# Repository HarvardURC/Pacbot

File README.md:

# PacBot
Repository for the Harvard Undergraduate Robotics Club's PacBot team

> NOTE: Because this repository includes submodules, it should be cloned using `git clone --recursive`.

The rules for PacBot and helpful images can be found at our website: https://harvardrobotics.com/pacbots

Codebase for 2021-2022 can be found in the ***master*** branch. Codebases for past years can be found in their respective branches.

The current Pacman game code can be found in 'src/gameEngine'. The README there describes how to run the game.

The code for the Harvard robotics team's bot can be found in the 'src/botCode' folder (if you're looking for inspiration).

Documentation for participating teams regarding the game board/arena, bot designs from past years, and how to communicate with the game can be found in the 'docs' directory. Baseline code is provided here that teams can use to code their bots.

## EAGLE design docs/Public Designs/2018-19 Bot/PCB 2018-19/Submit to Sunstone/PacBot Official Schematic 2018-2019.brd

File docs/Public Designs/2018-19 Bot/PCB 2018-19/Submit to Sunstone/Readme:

LAYER DESCRIPTIONS

tplace (21), tnames (25): Top silk layer

bplace (22), bnames (26): Bottom silk layer

holes (45): Reference for where holes should be placed so that PCB can be fastened by nut and bolt

reference (49): For personal reference (not to be printed)

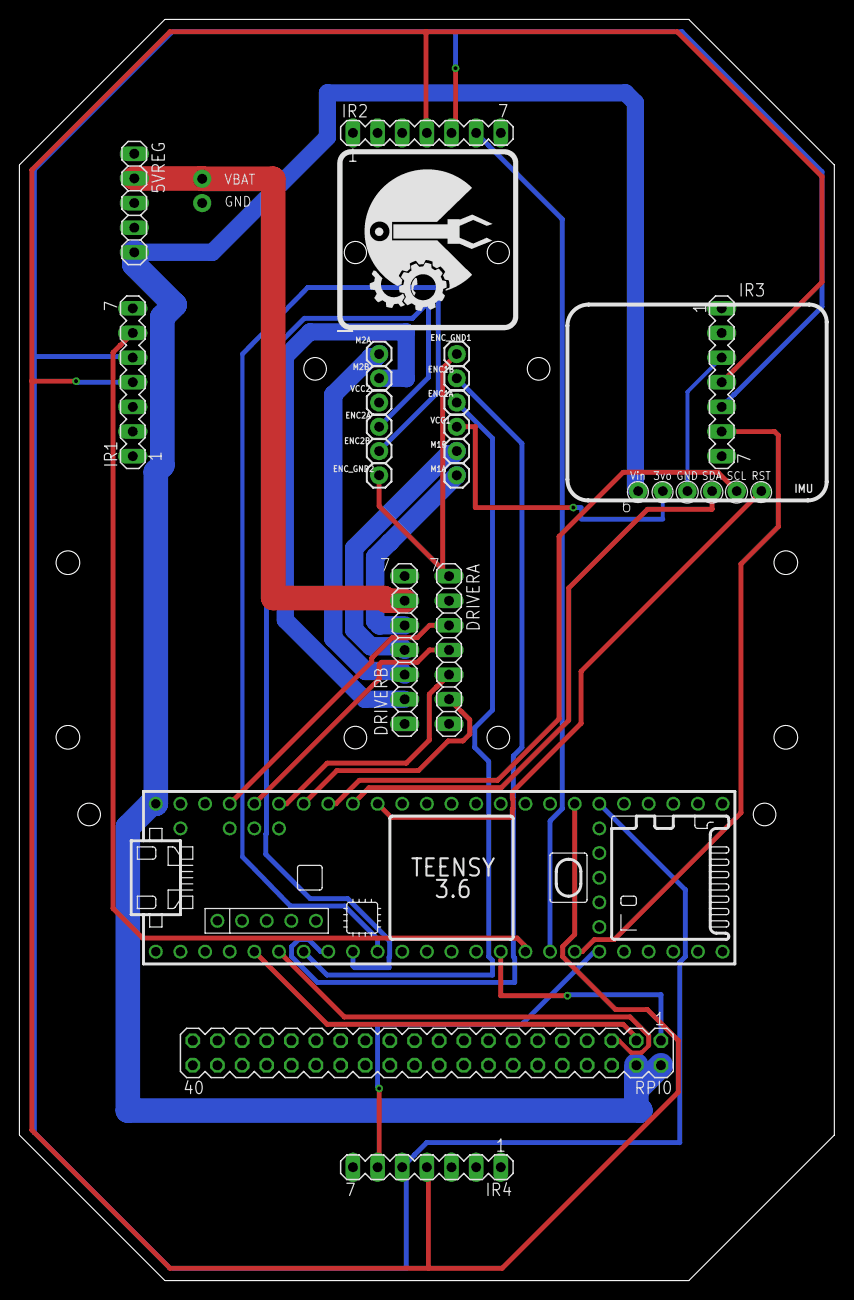
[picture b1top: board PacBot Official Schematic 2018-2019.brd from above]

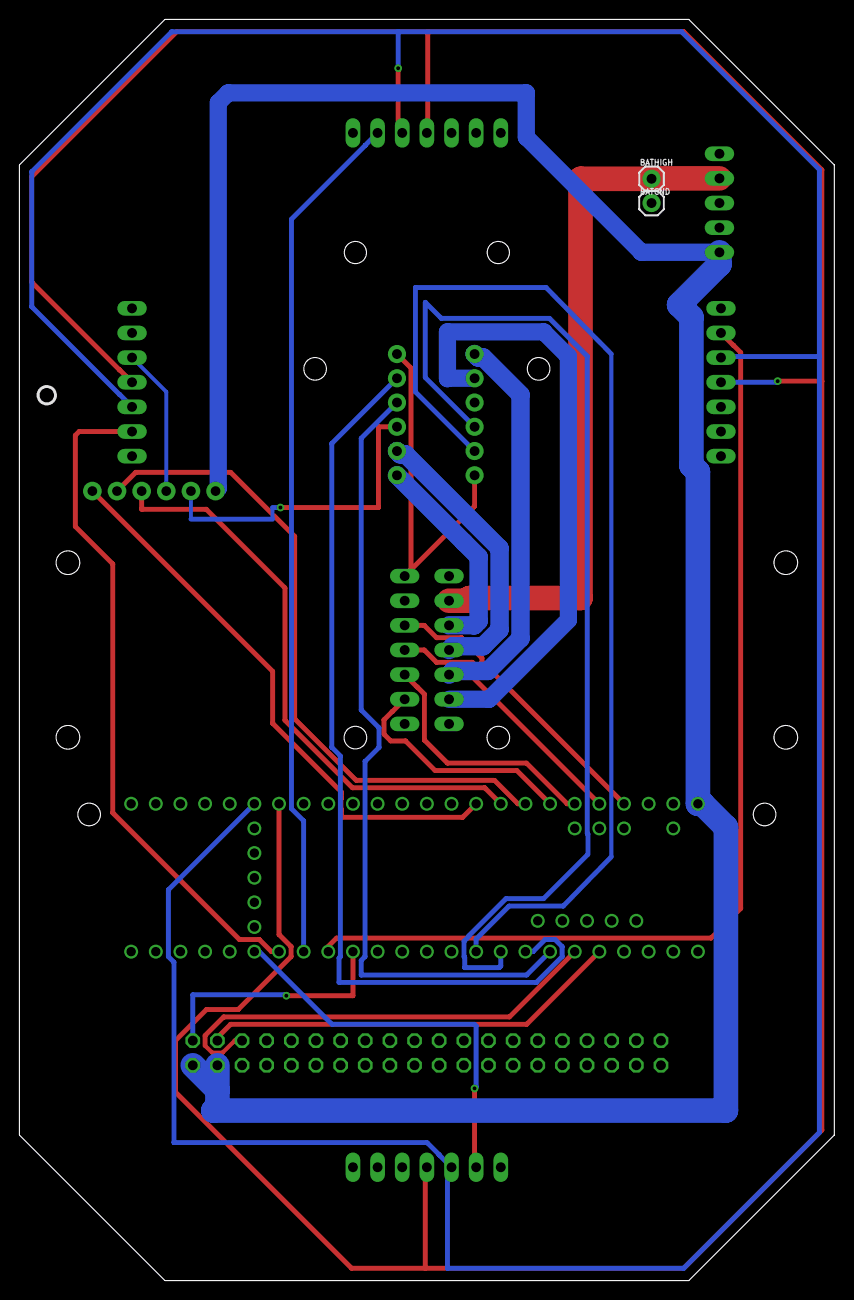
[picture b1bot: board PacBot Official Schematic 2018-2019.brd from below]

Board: 2 copper layers, 84.0 x 130.0 mm, 25 parts (3 on the bottom side), 27 nets.

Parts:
5VREG: 1X05
BATGND: 1X01
BATHIGH: 1X01
DRIVERA: 1X07
DRIVERB: 1X07
ENC1A, ENC1B, ENC2A, ENC2B: 1X01
ENC_GND1, ENC_GND2: 1X01
IMU: 1X06_ROUND_76
IR1, IR2, IR3, IR4: MA07-1
M1A, M1B, M2A, M2B: 1X01
RPI0: MA20-2
U$1: TEENSY_3.5/3.6
U$65: PCBFEAT-REV-040
VCC1, VCC2: 1X01

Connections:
3.3V: DRIVERA.2, DRIVERA.7, IMU.2, IR1.2, IR2.2, IR3.2, IR4.2, RPI0.1, U$1.3V3, U$1.3V3_LO, VCC1.1, VCC2.1
5.0V: 5VREG.5, IMU.1, RPI0.2, RPI0.4, U$1.VIN
AENBL: DRIVERA.5, U$1.21/A7
APHASE: DRIVERA.6, U$1.20/A6
BENBL: DRIVERA.3, U$1.23/A9
BPHASE: DRIVERA.4, U$1.22/A8
GND: 5VREG.3, 5VREG.4, BATGND.1, DRIVERA.1, DRIVERB.7, ENC_GND1.1, ENC_GND2.1, IMU.3, IR1.3, IR2.3, IR3.3, IR4.3, RPI0.6, RPI0.9, RPI0.14, RPI0.20, RPI0.25, RPI0.30, RPI0.34, RPI0.39, U$1.AGND, U$1.GND, U$1.GND2
unnamed: ENC1A.1, U$1.5
unnamed: IR2.6, U$1.25
unnamed: RPI0.3, U$1.3/CANTX
unnamed: IR3.6, U$1.26
unnamed: ENC1B.1, U$1.6
unnamed: RPI0.5, U$1.4/CANRX
unnamed: IR4.6, U$1.27
unnamed: DRIVERB.5, M1A.1
unnamed: DRIVERB.4, M1B.1
unnamed: DRIVERB.3, M2A.1
unnamed: DRIVERB.2, M2B.1
unnamed: ENC2A.1, U$1.7
unnamed: ENC2B.1, U$1.8
unnamed: IR1.6, U$1.24
RST_5V: IMU.6, U$1.17/A3
SCL1: IR1.5, IR2.5, IR3.5, IR4.5, U$1.38/A19
SCL_5V: IMU.5, U$1.19/A5/SCL
SDA1: IR1.4, IR2.4, IR3.4, IR4.4, U$1.39/A20
SDA_5V: IMU.4, U$1.18/A4/SDA
VBAT: 5VREG.2, BATHIGH.1, DRIVERB.6

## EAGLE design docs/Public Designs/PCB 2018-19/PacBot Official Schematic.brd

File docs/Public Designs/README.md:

# Harvard PacBot Design Overview 2018-19
(PCB design files and schematic can be found in public PacBot Design Folder)

## Electrical Components
-1 Raspberry Pi Zero W

-1 Teensy 3.5

-1 PCB

-1 IMU

-Assorted capacitors, resistors, wires

-4 IR Sensors

-2 Magnetic encoder pairs

-2 Motors

-1 Motor Driver

-Li-Po Battery

(specific links to components can be found at https://docs.google.com/spreadsheets/d/1ZO9OBoGcNkOdx6GaBkAFo6AWodeVCOaCXKic-0er2z0/edit?usp=sharing)

## Mechanical Components
-Wheels/Ball Casters

-3D Printed Battery Clip

## Code
All code can be found in the accompanying folders in this repo. We recommend looking at code from 2018-2019 because this year's code will be undergoing maintenance between now and the competition.

## Broad Overview
As the core processors for the bot, a Raspberry Pi Zero W and Teensy 3.5 were used. Nearly all of our high level and low level code ran off of our Raspberry Pi Zero W; the teensy was mainly used to interface with the encoders and other sensors. The entire bot was centered around the PCB. The motors directly attached to the PCB using small brackets, and all of the electrical components were soldered on in some manner. Although the schematic of the electrical components and the PCB design (which are in this folder) give an idea of the set up of our bot, we unfortunately do not have a SolidWorks design of our 2018-19 bot. A few photos of the 2018-19 bot in this folder help give a picture of the overall design. Further information (including a SolidWorks cad file) regarding our 2020-21 bot will be provided soon to supplement this overview.

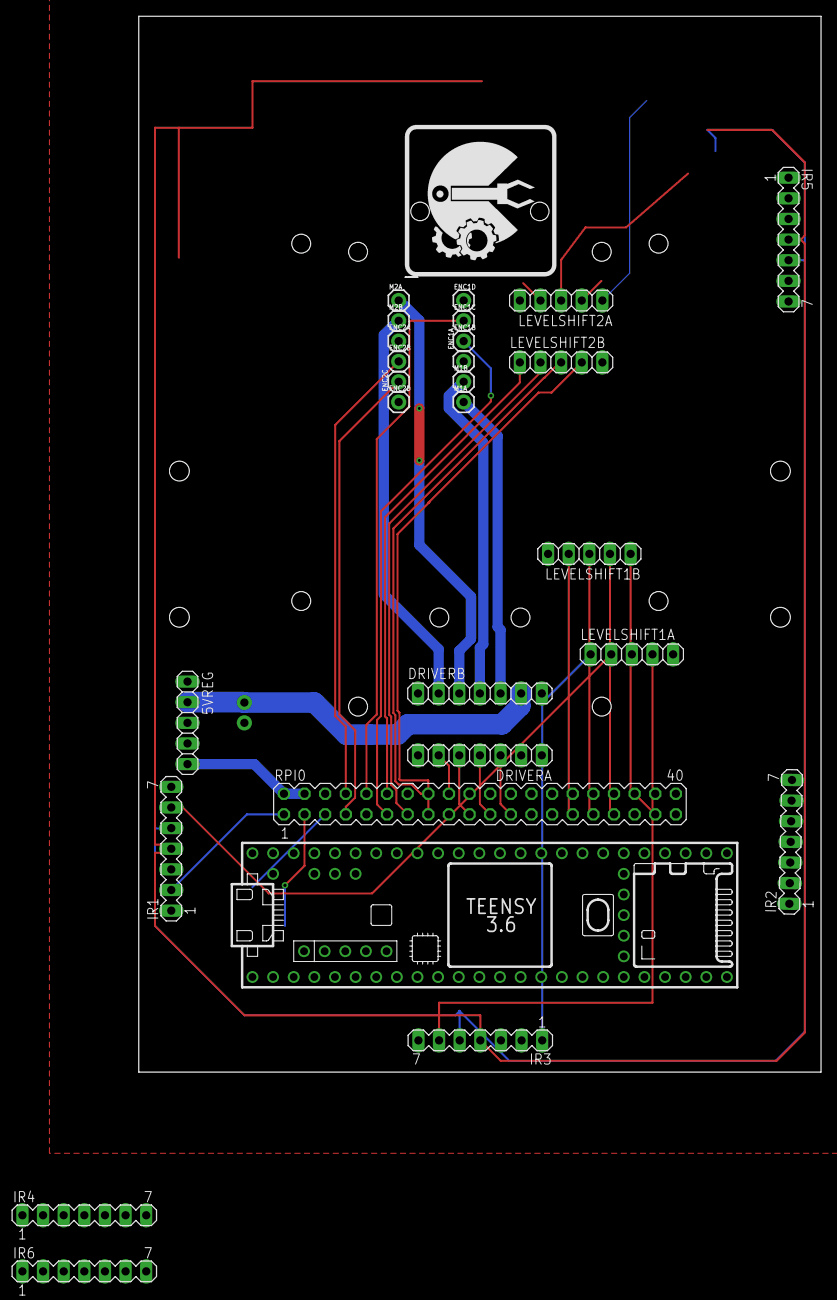
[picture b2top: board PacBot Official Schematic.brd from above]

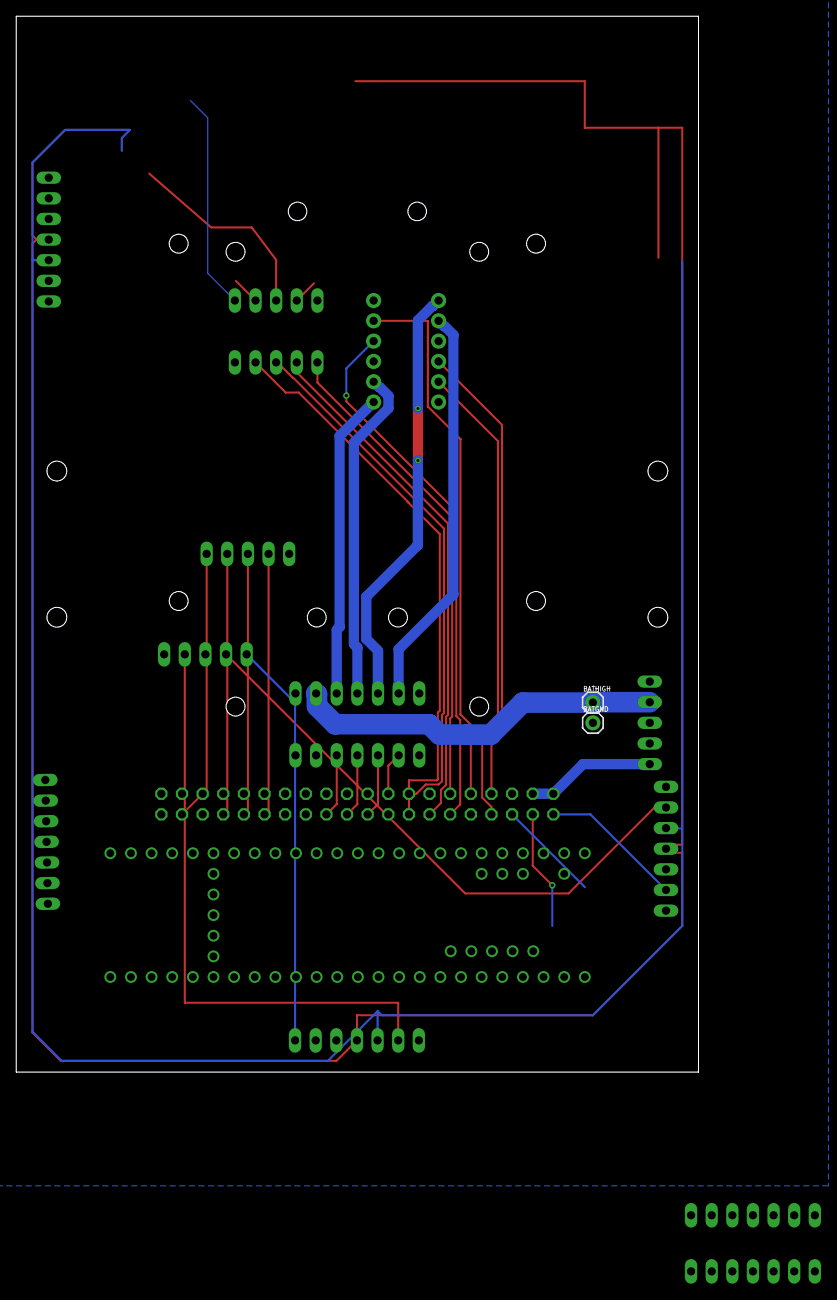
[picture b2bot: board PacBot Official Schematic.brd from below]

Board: 2 copper layers, 84.0 x 130.0 mm, 29 parts (2 on the bottom side), 32 nets.

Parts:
5VREG: 1X05
BATGND: 1X01
BATHIGH: 1X01
DRIVERA: 1X07
DRIVERB: 1X07
ENC1A, ENC1B, ENC1C, ENC1D, ENC2A, ENC2B, ENC2C, ENC2D: 1X01
IR1, IR2, IR3, IR4, IR5, IR6: MA07-1
LEVELSHIFT1A, LEVELSHIFT1B, LEVELSHIFT2A, LEVELSHIFT2B: 1X05
M1A, M1B, M2A, M2B: 1X01
RPI0: MA20-2
U$1: TEENSY_3.5/3.6

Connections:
2.8V: IR2.1, IR3.1, IR4.1, IR5.1, IR6.1, LEVELSHIFT1A.1, LEVELSHIFT2A.1
3.3V: DRIVERA.2, DRIVERA.7, ENC1A.1, ENC2A.1, IR1.2, IR2.2, IR3.2, IR4.2, IR5.2, IR6.2, LEVELSHIFT1B.5, LEVELSHIFT2B.5, RPI0.1
5V: 5VREG.5, RPI0.2, RPI0.4
AENBL: DRIVERA.5, RPI0.19
APHASE: DRIVERA.6, RPI0.18
BENBL: DRIVERA.3, RPI0.23
BPHASE: DRIVERA.4, RPI0.21
GND: 5VREG.3, 5VREG.4, BATGND.1, DRIVERA.1, DRIVERB.7, ENC1D.1, ENC2D.1, IR1.3, IR2.3, IR3.3, IR4.3, IR5.3, IR6.3, RPI0.6, RPI0.9, RPI0.14, RPI0.20, RPI0.25, RPI0.30, RPI0.34, RPI0.39
unnamed: ENC1B.1, RPI0.11
unnamed: IR4.6, LEVELSHIFT2A.2
unnamed: LEVELSHIFT2B.2, RPI0.13
unnamed: LEVELSHIFT2B.1, RPI0.12
unnamed: DRIVERB.5, M1A.1
unnamed: DRIVERB.4, M1B.1
unnamed: DRIVERB.3, M2A.1
unnamed: DRIVERB.2, M2B.1
unnamed: ENC1C.1, RPI0.10
unnamed: ENC2B.1, RPI0.8
unnamed: ENC2C.1, RPI0.7
unnamed: IR5.6, LEVELSHIFT2A.3
unnamed: IR6.6, LEVELSHIFT2A.4
unnamed: LEVELSHIFT1B.4, RPI0.29
unnamed: LEVELSHIFT1B.3, RPI0.31
unnamed: LEVELSHIFT1B.2, RPI0.33
unnamed: LEVELSHIFT1B.1, RPI0.37
unnamed: LEVELSHIFT2B.4, RPI0.15
unnamed: LEVELSHIFT2B.3, RPI0.16
unnamed: IR1.6, LEVELSHIFT1A.2
unnamed: IR3.6, LEVELSHIFT1A.4
SCL: IR1.5, IR2.5, IR3.5, IR4.5, IR5.5, IR6.5, RPI0.5
SDA: IR1.4, IR2.4, IR3.4, IR4.4, IR5.4, IR6.4, RPI0.3
VBAT: 5VREG.2, BATHIGH.1, DRIVERB.6

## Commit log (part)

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2017-12-02 errors fixed
2017-12-02 encoders changed
2017-12-03 grid and legends added
2017-12-03 Capitalization fixed
2018-01-11 Add to gameEngine README instructions.
2018-01-11 Add to gameEngine README instructions. (#24)
2018-01-27 grids for path types renames. Working on controllers all motors for bot movement. Testing will start as soon as the bot is assembled
2018-01-28 fix camera reader vol1
2018-02-17 latest changes
2018-02-24 none
2018-03-03 latest commit from pi
2018-03-03 encoderTest edited
2018-03-03 encoders
2018-03-03 encoders changes
2018-03-24 PID changed
2018-03-24 test
2018-03-31 motors
2018-03-31 motors2
2018-03-31 motorTest changes
2018-04-07 wall follow
2018-04-07 wall follow edited
2018-04-14 Vision Code
2018-04-14 Transform code!
2018-04-14 motors.py changed
2018-04-14 motors edited
2018-04-14 add dots
2018-04-21 bot tracking works
2018-04-21 motors updated
2018-04-21 motors syntax fixed
2018-04-21 motors.py
2018-04-21 motor logic restructure hand off
2018-04-21 motors2 updated
2018-04-21 straight inserted
2018-04-21 tracking works
2018-04-21 single sensor modes added
2018-04-21 add keyboard simulator
2018-04-21 extra condition addition hand off
2018-04-21 new condition added for tie breaking
2018-04-21 P value updated
2018-04-21 cleanup
2018-04-21 camels
2018-04-21 turning code
2018-04-22 conditions
2018-04-22 clean up
2018-04-22 yeeehaw
2018-04-23 test.py
2018-04-23 new encoder code
2018-04-23 old encoders
2018-04-23 current
2018-04-23 latest
2018-04-23 c encoders
2018-04-23 encoder test
2018-04-23 python c interface
2018-04-24 pigpio
2018-04-24 go back to last commit
2018-04-24 library
2018-04-24 encoder callback
2018-04-24 encoder callback needs to be in function
2018-04-24 make setup executable
2018-04-24 rmeove print
2018-04-24 argsss
2018-04-24 change encoder libraries
2018-04-25 push
2018-04-26 no camera low level
2018-04-26 new motor tunings
2018-04-26 reverse direction
2018-04-26 vision works
2018-04-26 added fail safe
2018-04-26 diagonal sensors
2018-04-26 make vision image smaller
2018-04-26 latest, without diagonal sensors
2018-04-26 Low level (#26)
    * added the initial codes for super low level control
    * cleanup
    * work on lowLevelModule
    * GPIO helpers updated to add millis function. PID library added
    * motor.py modified to supoort speed sepcification. motorTest modified correspondingly. PID.py modified to add output() module. WallFollowTest added. The scope of variables need to determined while t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
    * fixed indentation in wallFollowTest
2018-04-26 latest changes from pi
2018-04-28 latest code from pi
2018-04-28 change to heuristics
2018-04-28 latest from pi
2019-04-06 working things
2019-06-29 Add working arena 2018-2019
2019-10-12 Overview changes
2019-10-20 Added 2019-2020
2019-10-29 Updated Docs
2020-01-27 Added PCB Files
2020-02-23 Added blinking to vulnerable ghosts and cherry spawning
2020-10-24 copying 2019-2020 into 2020-2021
2020-10-27 added robomodules submodule
2020-10-27 changing submodule stuff
2020-10-28 updating gitignore for c++
2020-10-28 adding deque and pid stuff
2020-10-28 more progress on pid and deque
2020-10-28 seems like a working pid class to me. Untested though
2020-10-28 copying in rotaryEncoder
2020-10-28 adding readmes
2020-10-28 adding motor and tof templates, no functionality yet
2020-10-28 adding imu file
2020-10-29 robot state implemented, robotstatehistory.hpp almost finished
2020-10-31 more stuff
2020-11-01 rsh done, untested still
2020-11-01 deque stuff
2020-11-01 twas in the wrong branch
2020-11-01 addded globalState
2020-11-02 calling globalstate from master
2020-11-07 adding botcode stuff
2021-02-01 added Makefile. Still not working; deque is fucked, probably other stuff too
2021-02-01 try running this to see the error: g++ -std=c++14 -c -Wall utils/conversions.cpp dataTypes/deque.cpp controllers/pid.cpp
2021-02-10 initial bfs work in c++
2021-02-13 it compiles :)
2021-02-13 Bump httplib2 from 0.9.2 to 0.19.0
    Bumps [httplib2](https://github.com/httplib2/httplib2) from 0.9.2 to 0.19.0.
    - [Release notes](https://github.com/httplib2/httplib2/releases)
    - [Changelog](https://github.com/httplib2/httplib2/blob/master/CHANGELOG)
    - [Commits](https://github.com/httplib2/httplib2/compare/0.9.2...v0.19.0)
2021-02-13 Bump psutil from 5.5.1 to 5.6.6
    Bumps [psutil](https://github.com/giampaolo/psutil) from 5.5.1 to 5.6.6.
    - [Release notes](https://github.com/giampaolo/psutil/releases)
    - [Changelog](https://github.com/giampaolo/psutil/blob/master/HISTORY.rst)
    - [Commits](https://github.com/giampaolo/psutil/compare/release-5.5.1...release-5.6.6)
2021-02-13 Bump pillow from 5.4.1 to 7.1.0
    Bumps [pillow](https://github.com/python-pillow/Pillow) from 5.4.1 to 7.1.0.
    - [Release notes](https://github.com/python-pillow/Pillow/releases)
    - [Changelog](https://github.com/python-pillow/Pillow/blob/master/CHANGES.rst)
    - [Commits](https://github.com/python-pillow/Pillow/compare/5.4.1...7.1.0)
2021-02-13 fixing some imports
2021-02-13 updating loop()
2021-02-13 updating stuff
2021-02-14 moving back to custom home-made deque
2021-02-20 sensors/actuators
2021-02-20 sensors/actuators2
2021-02-20 sensors/actuators3
2021-02-20 sensor readmes added
2021-02-20 comments about k_predict
2021-02-20 comment reformatted
2021-02-23 clean up files/edit READMEs
2021-02-23 theoretically a wall follower
2021-02-23 makefile
2021-02-23 commented out est/updater includes
2021-02-23 fixing wall follower
2021-02-23 tof names
2021-02-23 changing to .h
2021-02-23 changing sensors/motor
2021-02-23 more changes
2021-02-23 makefile update
2021-02-23 im dumb
2021-02-23 adding prints
2021-02-23 stdio
2021-03-19 Bump pillow from 5.4.1 to 8.1.1
    Bumps [pillow](https://github.com/python-pillow/Pillow) from 5.4.1 to 8.1.1.
    - [Release notes](https://github.com/python-pillow/Pillow/releases)
    - [Changelog](https://github.com/python-pillow/Pillow/blob/master/CHANGES.rst)
    - [Commits](https://github.com/python-pillow/Pillow/compare/5.4.1...8.1.1)
2021-03-20 updated makefile and global sensors/actuators
2021-03-26 Bump pyyaml from 3.13 to 5.4
    Bumps [pyyaml](https://github.com/yaml/pyyaml) from 3.13 to 5.4.
    - [Release notes](https://github.com/yaml/pyyaml/releases)
    - [Changelog](https://github.com/yaml/pyyaml/blob/master/CHANGES)
    - [Commits](https://github.com/yaml/pyyaml/compare/3.13...5.4)
2021-04-10 fixed deque
2021-04-17 new branch
2021-05-16 some edits
2021-05-21 aww man we looking better
2021-05-22 testing
2021-05-22 fixed dque, and now pid is passing too thank god
2021-05-23 did someone say testssss
2021-05-25 oh, did someone say that the particle filter is working? Damnnnn
2021-05-25 some updated to particle filter, so it works more nicely with stuff that uses extra stuff in the past
2021-05-26 more edits
2021-05-26 oops lolll
2021-06-08 Bump pillow from 5.4.1 to 8.2.0
    Bumps [pillow](https://github.com/python-pillow/Pillow) from 5.4.1 to 8.2.0.
    - [Release notes](https://github.com/python-pillow/Pillow/releases)
    - [Changelog](https://github.com/python-pillow/Pillow/blob/master/CHANGES.rst)
    - [Commits](https://github.com/python-pillow/Pillow/compare/5.4.1...8.2.0)
    ---
    updated-dependencies:
2021-09-08 Bump pillow from 5.4.1 to 8.3.2
    Bumps [pillow](https://github.com/python-pillow/Pillow) from 5.4.1 to 8.3.2.
    - [Release notes](https://github.com/python-pillow/Pillow/releases)
    - [Changelog](https://github.com/python-pillow/Pillow/blob/master/CHANGES.rst)
    - [Commits](https://github.com/python-pillow/Pillow/compare/5.4.1...8.3.2)
    ---
    updated-dependencies:
2021-10-24 frightened ghosts reset on respawn
2021-10-27 created 2020-2021 branch
2021-10-27 deletions
2021-10-27 2017-2018 branch created
2021-10-27 2018-2019 branch created
2021-10-27 2019-2020 created
2021-10-27 restructured code base for 2021-2022
2021-10-28 some readme updates
2021-10-28 added submodule
2021-10-31 new orange respawn path, game ends even if gghosts are frightened
2021-11-14 variables.py comments, changed terminal print outs, made visualized game fit on screen
2021-11-14 resizing through command line argument
2021-11-17 added environment.yml
2021-11-17 edited the readme
2021-11-17 moved environment
2021-11-18 new env
2021-11-21 commented ghostAgent.py
2021-11-21 added various additional comments
2021-11-24 shuffling documentation
2021-11-24 updating docs
2021-12-05 more documentation
2022-01-02 remove folders
2022-01-02 clean up more
2022-01-02 added reqs.txt
2022-01-03 some docs updates
2022-01-04 update ghost paths
2022-01-04 update ghost movement
2022-01-04 reshaping through command line
2022-01-04 game bugs fixed
2022-01-04 fruit not rn
2022-01-06 working on fruit, updating messages
2022-01-07 updated grid location
2022-01-07 updated arena documentation
2022-01-16 remove robomodules submodule
2022-01-16 submodule added back
2022-01-21 updated readme for game engine
2022-01-26 bot PCB added
2022-01-26 pcb start
2022-01-26 commited a few more files
2022-01-26 removed PCB dir
2022-01-30 added board outline
2022-02-06 added the vias and guiding labels
2022-02-06 init branch
2022-02-09 shuffle public design docs
2022-02-09 Revert "shuffle public design docs"
    This reverts commit 1f18fdc1b2d93b0dda7e0a9332dcd78fc0c3774f.
2022-02-09 shuffle docs
2022-02-09 2020-21 Bot added
2022-02-09 2020-21 README added
2022-02-09 docs added for 2020-21 bot
2022-02-09 chance jpg
2022-02-09 change
2022-02-09 remove messages
2022-02-09 update to botCode
2022-02-13 FIxed cherry
2022-02-14 kinda working
2022-02-14 small changes by Tom
2022-02-20 gitignore, no DS Store
2022-02-20 ghosts reverse when changing state between chase + scatter
2022-02-20 reverses direction on frighten
2022-02-20 Added Teensy, holes need to be moved
2022-02-24 Holes moved, some more components added
2022-02-25 fixed rawdata for new I2C bus
2022-02-27 updated teensy code
2022-02-27 PCB updated
2022-02-27 fixed cherry repeat bug
2022-02-27 started on launch script
2022-02-27 removed unused import. gameEngine runs again
2022-02-27 launch.sh now closes the tabs it creates
2022-02-27 PCB components placed
2022-03-02 finished sensors script
2022-03-06 updated pcb
2022-03-06 back up included
2022-03-06 working on PCB
2022-03-09 update kicad
2022-03-11 finished pcb
2022-03-12 schematic updated
2022-03-12 visualize address updated
2022-03-27 kicad updated
2022-03-27 something?
2022-03-28 Tom changes
2022-03-28 gameState.py updated for ghost reversal
2022-03-28 ghostAgent.py updated for ghost reversal
2022-03-30 change serial
2022-03-30 read too
2022-03-31 Sensors class created for teensy
2022-03-31 sensors updated
2022-03-31 reset encoders
2022-03-31 to do updated
2022-04-05 stuff
2022-04-05 teensy code
2022-04-05 pins updated
2022-04-05 updated rpi code
2022-04-06 update sensors
2022-04-06 getting to work
2022-04-06 local updates
2022-04-08 updated code
2022-04-08 editing motors
2022-04-13 updates to low level
2022-04-13 motor test update
2022-04-13 updated motors
2022-04-13 updated sensors
2022-04-13 sensors
2022-04-13 Detects walls
2022-04-14 small updates
2022-04-14 Tweaks to turning functions to help correct via IR sensors
2022-04-16 most recent on bot
2022-04-16 init
2022-04-16 include init
2022-04-17 updates from bot
2022-04-20 possible motors update
2022-04-20 separating low and upper parts of game board
2022-04-20 no todo
2022-04-20 visualier updated
2022-04-20 ticks
2022-04-22 finishing arena
2022-08-06 added low level README
2022-08-06 remove swap file
2022-09-23 Bump protobuf from 3.19.1 to 3.19.5 in /src
    Bumps [protobuf](https://github.com/protocolbuffers/protobuf) from 3.19.1 to 3.19.5.
    - [Release notes](https://github.com/protocolbuffers/protobuf/releases)
    - [Changelog](https://github.com/protocolbuffers/protobuf/blob/main/generate_changelog.py)
    - [Commits](https://github.com/protocolbuffers/protobuf/compare/v3.19.1...v3.19.5)
    ---
    updated-dependencies:
2025-06-17 Bump protobuf from 3.19.1 to 4.25.8 in /src
    Bumps [protobuf](https://github.com/protocolbuffers/protobuf) from 3.19.1 to 4.25.8.
    - [Release notes](https://github.com/protocolbuffers/protobuf/releases)
    - [Changelog](https://github.com/protocolbuffers/protobuf/blob/main/protobuf_release.bzl)
    - [Commits](https://github.com/protocolbuffers/protobuf/compare/v3.19.1...v4.25.8)
    ---
    updated-dependencies:

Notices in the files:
parts and their libraries:
SparkFun-Connectors: Licensing: Creative Commons ShareAlike 4.0 International - https://creativecommons.org/licenses/by-sa/4.0
microbuilder: This work is placed in the public domain, and may be freely used for commercial and non-commercial work with the following conditions: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
